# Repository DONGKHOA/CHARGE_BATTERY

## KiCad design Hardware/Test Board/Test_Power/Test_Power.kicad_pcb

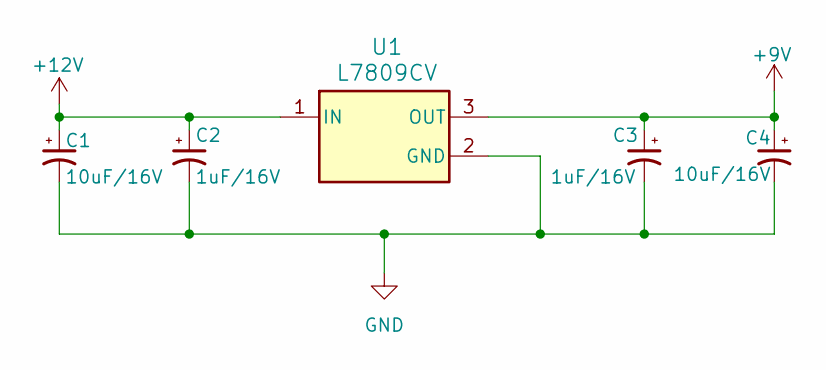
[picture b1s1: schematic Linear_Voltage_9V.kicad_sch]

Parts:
C1, C4: 10uF/16V; Tan_Cap_A
C2, C3: 1uF/16V; Tan_Cap_A
U1: L7809CV; TO-220-3

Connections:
+9V: C3.1, C4.1, U1.3 (OUT); also elsewhere on the board
+12V: C1.1, C2.1, U1.1 (IN); also elsewhere on the board

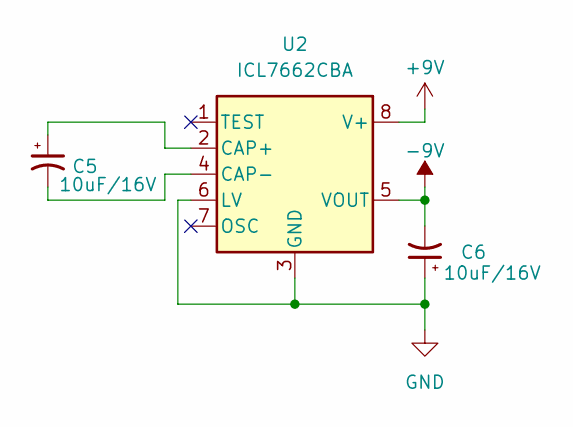
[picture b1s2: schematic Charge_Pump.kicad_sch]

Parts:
C5, C6: 10uF/16V; Tan_Cap_A
U2: ICL7662CBA; SOIC-8

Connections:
+9V: U2.8 (V+); also elsewhere on the board
-9V: C6.2, U2.5 (VOUT); also elsewhere on the board
unnamed: C5.1, U2.2 (CAP+)
unnamed: C5.2, U2.4 (CAP-)

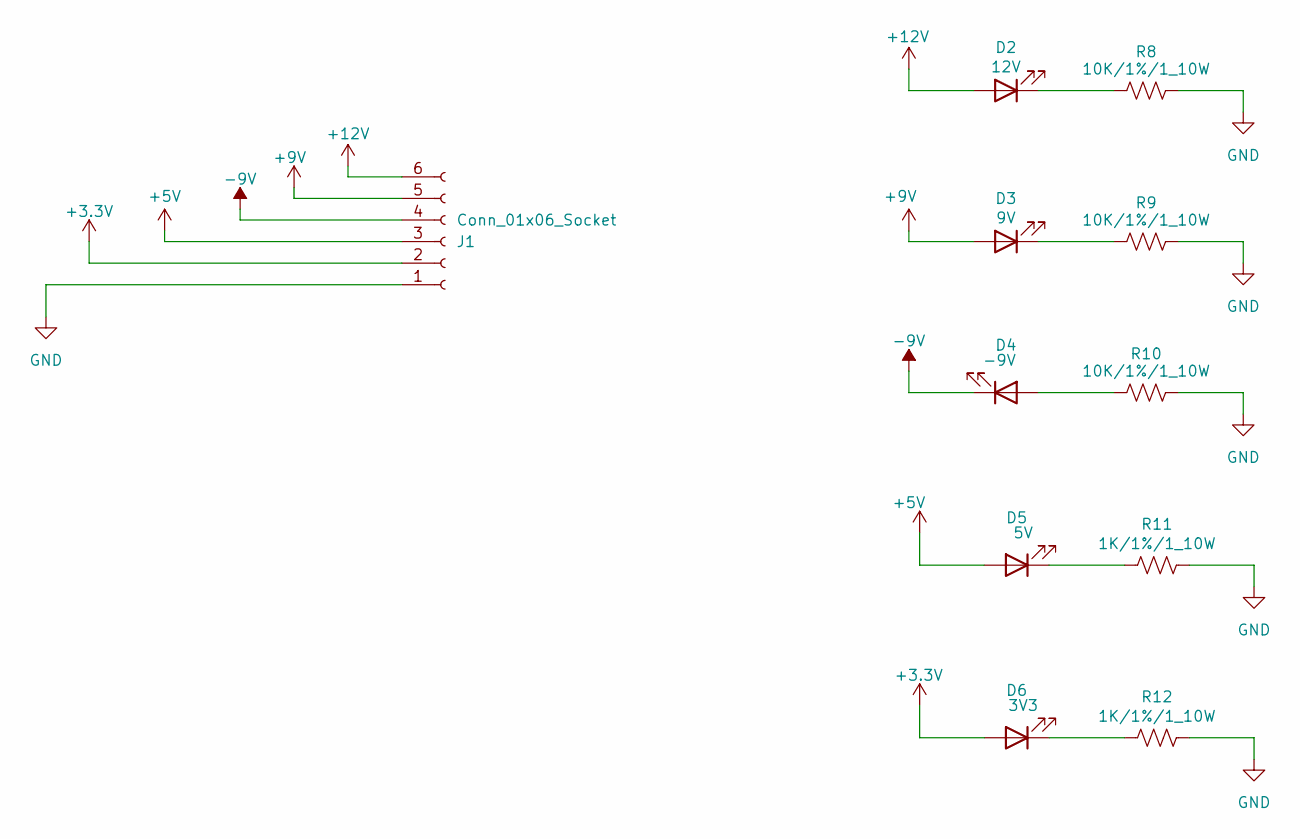
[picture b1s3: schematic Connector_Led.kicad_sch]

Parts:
D2: 12V; LED_0805
D3: 9V; LED_0805
D4: -9V; LED_0805
D5: 5V; LED_0805
D6: 3V3; LED_0805
J1: Conn_01x06_Socket; PhoenixContact_MC_1,5_6-G-3.81_1x06_P3.81mm_Horizontal
R8, R9, R10: 10K/1%/1_10W; Res_0603
R11, R12: 1K/1%/1_10W; Res_0603

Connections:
+3.3V: D6.2 (A), J1.2; also elsewhere on the board
+5V: D5.2 (A), J1.3; also elsewhere on the board
+9V: D3.2 (A), J1.5; also elsewhere on the board
+12V: D2.2 (A), J1.6; also elsewhere on the board
-9V: D4.1 (K), J1.4; also elsewhere on the board
unnamed: D2.1 (K), R8.1
unnamed: D3.1 (K), R9.1
unnamed: D4.2 (A), R10.1
unnamed: D5.1 (K), R11.1
unnamed: D6.1 (K), R12.1

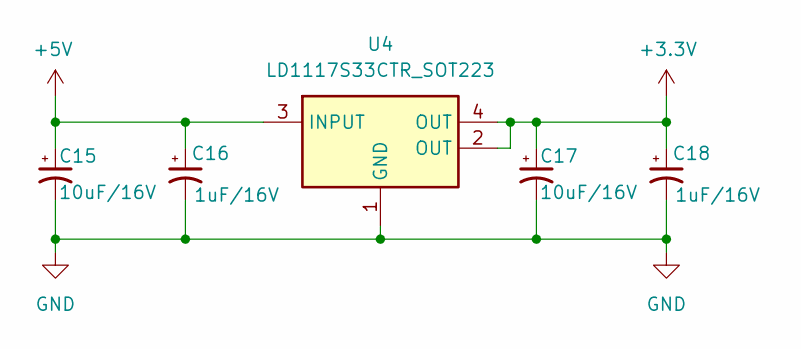
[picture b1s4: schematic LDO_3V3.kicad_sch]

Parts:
C15, C17: 10uF/16V; Tan_Cap_A
C16, C18: 1uF/16V; Tan_Cap_A
U4: LD1117S33CTR_SOT223; SOT-223

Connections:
+3.3V: C17.1, C18.1, U4.2 (OUT), U4.4 (OUT); also elsewhere on the board
+5V: C15.1, C16.1, U4.3 (INPUT); also elsewhere on the board

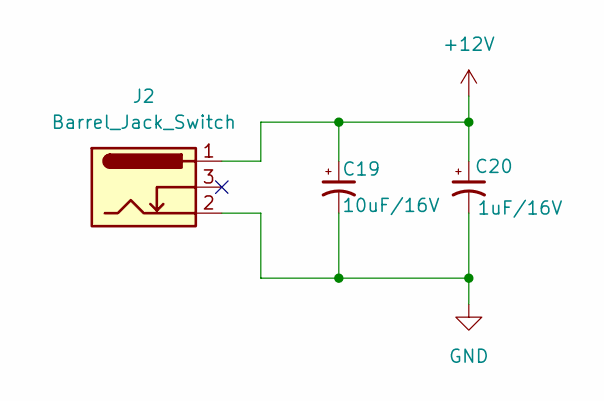
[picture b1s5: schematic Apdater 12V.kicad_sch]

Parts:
C19: 10uF/16V; Tan_Cap_A
C20: 1uF/16V; Tan_Cap_A
J2: Barrel_Jack_Switch; BarrelJack_GCT_DCJ200-10-A_Horizontal

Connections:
+12V: C19.1, C20.1, J2.1; also elsewhere on the board

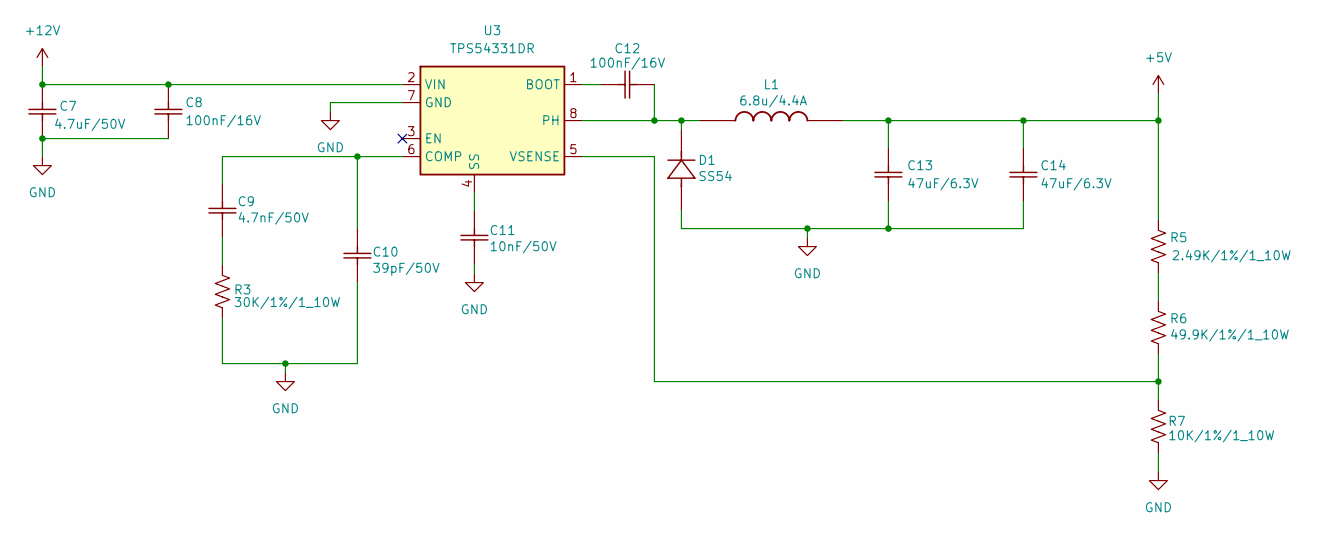
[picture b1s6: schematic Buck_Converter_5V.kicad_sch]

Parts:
C7: 4.7uF/50V; Ceramic_Cap_0805
C8, C12: 100nF/16V; Ceramic_Cap_0603
C9: 4.7nF/50V; Ceramic_Cap_0603
C10: 39pF/50V; Ceramic_Cap_0603
C11: 10nF/50V; Ceramic_Cap_0603
C13, C14: 47uF/6.3V; Ceramic_Cap_0805
D1: SS54; D_SMA
L1: 6.8u/4.4A; Inductor_6.8u_4.4A
R3: 30K/1%/1_10W; Res_0603
R5: 2.49K/1%/1_10W; Res_0603
R6: 49.9K/1%/1_10W; Res_0603
R7: 10K/1%/1_10W; Res_0603
U3: TPS54331DR; SOIC-8

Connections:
+5V: C13.2, C14.2, L1.2, R5.2; also elsewhere on the board
+12V: C7.2, C8.2, U3.2 (VIN); also elsewhere on the board
unnamed: C9.1, R3.2
unnamed: C12.2, D1.2 (K), L1.1, U3.8 (PH)
unnamed: R5.1, R6.2
unnamed: C12.1, U3.1 (BOOT)
unnamed: C9.2, C10.2, U3.6 (COMP)
unnamed: C11.2, U3.4 (SS)

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
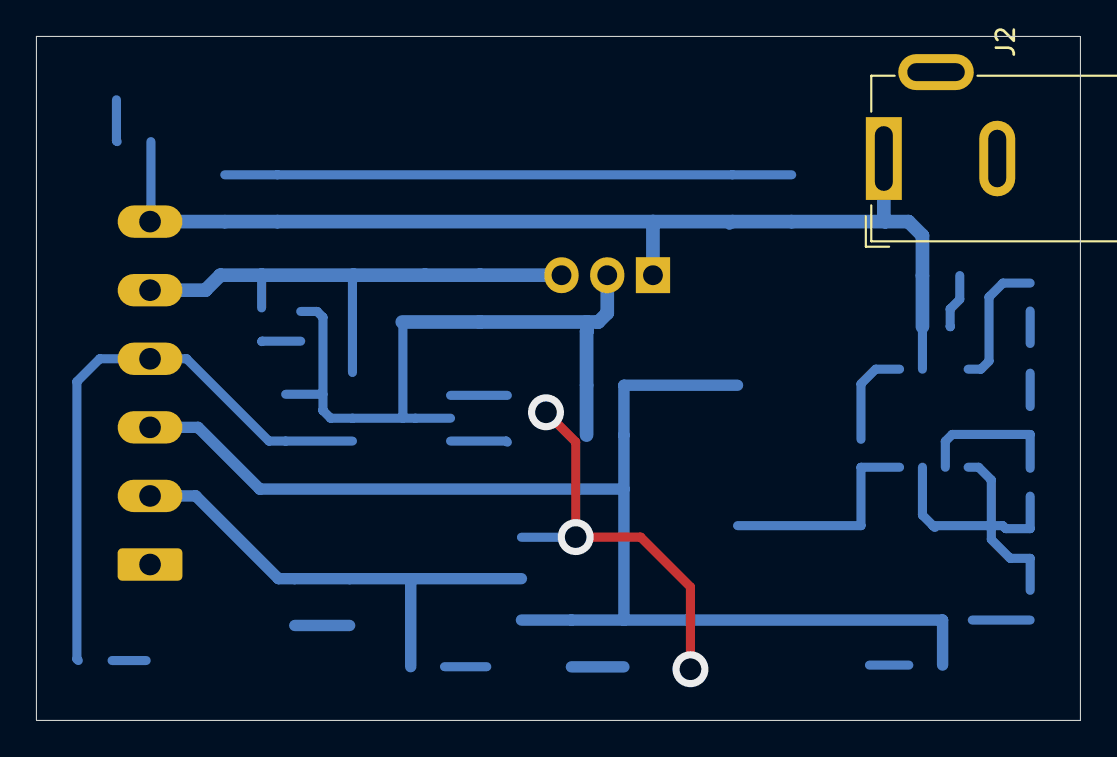
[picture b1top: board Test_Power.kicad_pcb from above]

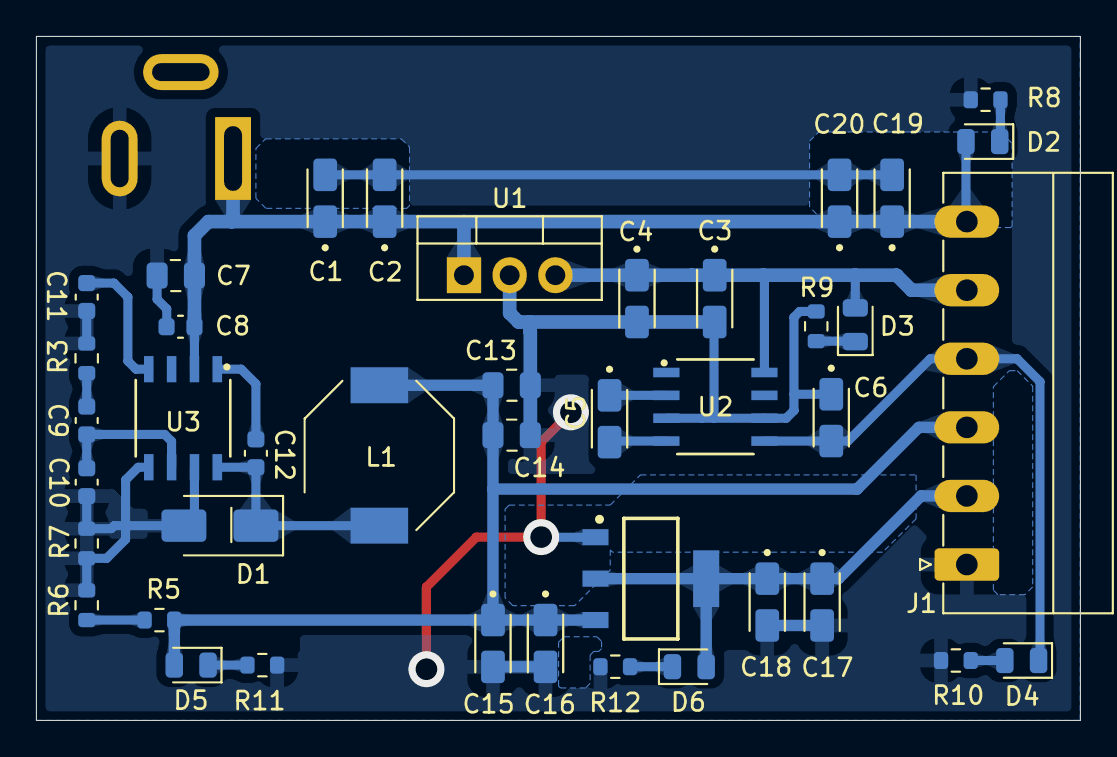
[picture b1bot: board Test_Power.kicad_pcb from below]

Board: 2 copper layers, 58.0 x 38.0 mm, 42 parts (41 on the bottom side), 19 nets.

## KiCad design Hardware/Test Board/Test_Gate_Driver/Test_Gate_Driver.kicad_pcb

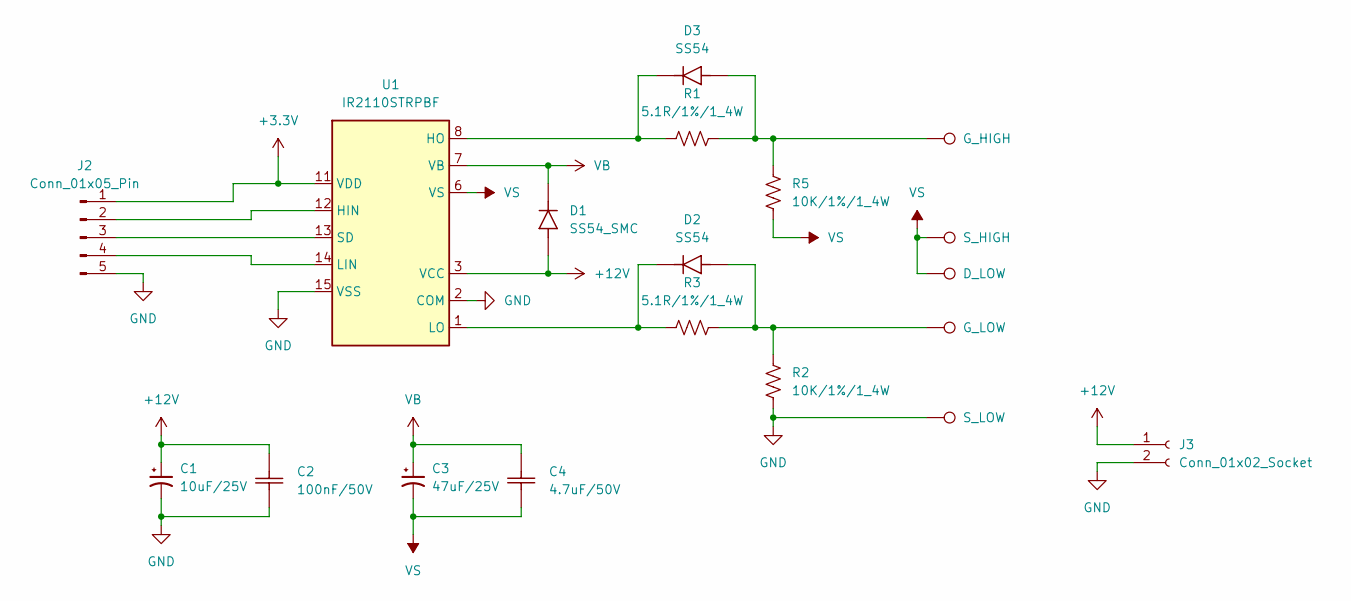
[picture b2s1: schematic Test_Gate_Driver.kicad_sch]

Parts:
C1: 10uF/25V; CP_Elec_4x5.4
C2: 100nF/50V; Ceramic_Cap_1206
C3: 47uF/25V; CP_Elec_6.3x5.4
C4: 4.7uF/50V; Ceramic_Cap_1206
D1: SS54_SMC; D_SMC
D2, D3: SS54; D_SMA
J2: Conn_01x05_Pin; PinHeader_1x05_P2.54mm_Vertical
J3: Conn_01x02_Socket; PinHeader_1x02_P2.54mm_Vertical
R1, R3: 5.1R/1%/1_4W; Res_1206
R2, R5: 10K/1%/1_4W; Res_1206
TP1: G_HIGH; TestPoint_Pad_3.0x3.0mm
TP2: S_HIGH; TestPoint_Pad_3.0x3.0mm
TP3: G_LOW; TestPoint_Pad_3.0x3.0mm
TP4: S_LOW; TestPoint_Pad_3.0x3.0mm
TP5: D_LOW; TestPoint_Pad_3.0x3.0mm
U1: IR2110STRPBF; SOP-16

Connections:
+3.3V: J2.1, U1.11 (VDD)
+12V: C1.1, C2.2, D1.1 (A), J3.1, U1.3 (VCC)
GND: C1.2, C2.1, J2.5, J3.2, R2.1, TP4.1, U1.2 (COM), U1.15 (VSS)
unnamed: D2.1 (A), R2.2, R3.2, TP3.1
unnamed: D2.2 (K), R3.1, U1.1 (LO)
unnamed: D3.1 (A), R1.2, R5.2, TP1.1
unnamed: D3.2 (K), R1.1, U1.8 (HO)
unnamed: J2.2, U1.12 (HIN)
unnamed: J2.3, U1.13 (SD)
unnamed: J2.4, U1.14 (LIN)
VB: C3.1, C4.1, D1.2 (K), U1.7 (VB)
VS: C3.2, C4.2, R5.1, TP2.1, TP5.1, U1.6 (VS)

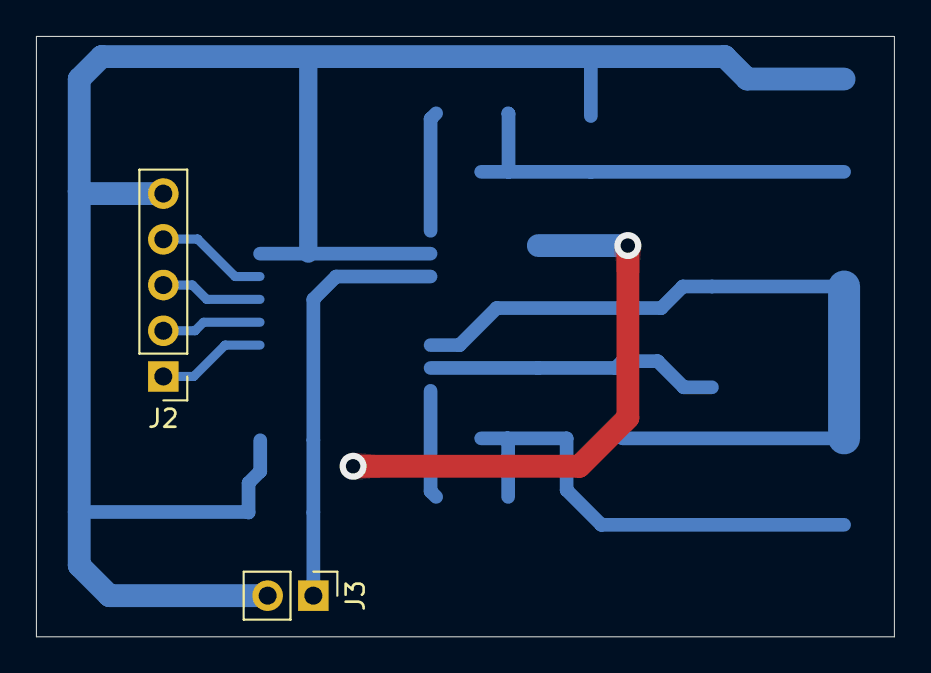
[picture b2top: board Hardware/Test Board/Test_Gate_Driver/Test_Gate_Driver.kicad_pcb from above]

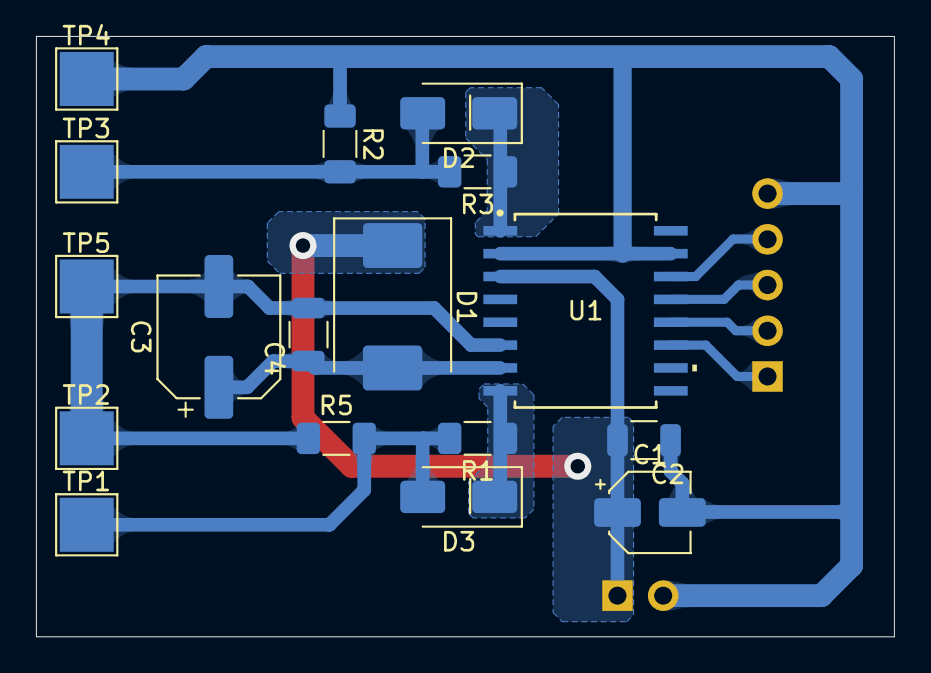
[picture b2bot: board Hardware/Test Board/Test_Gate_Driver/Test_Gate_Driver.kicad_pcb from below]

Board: 2 copper layers, 47.7 x 33.4 mm, 19 parts (17 on the bottom side), 12 nets.

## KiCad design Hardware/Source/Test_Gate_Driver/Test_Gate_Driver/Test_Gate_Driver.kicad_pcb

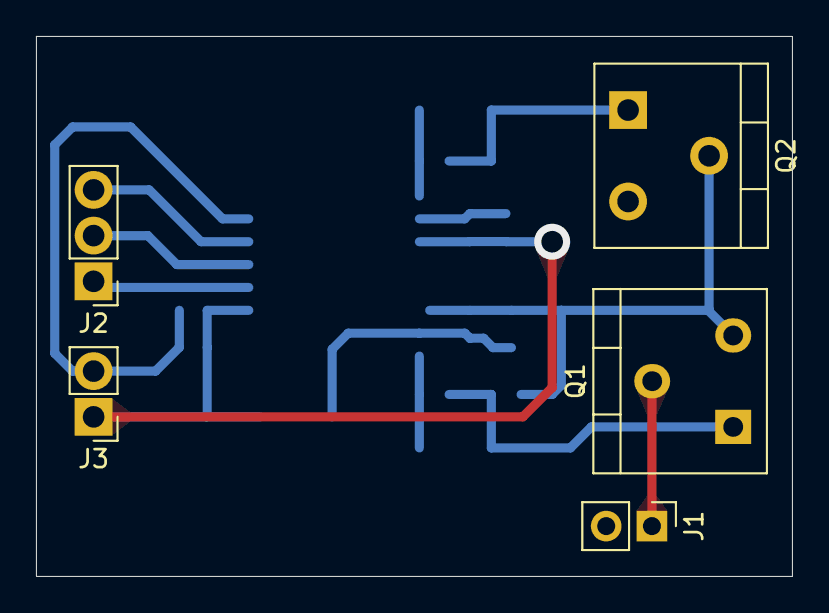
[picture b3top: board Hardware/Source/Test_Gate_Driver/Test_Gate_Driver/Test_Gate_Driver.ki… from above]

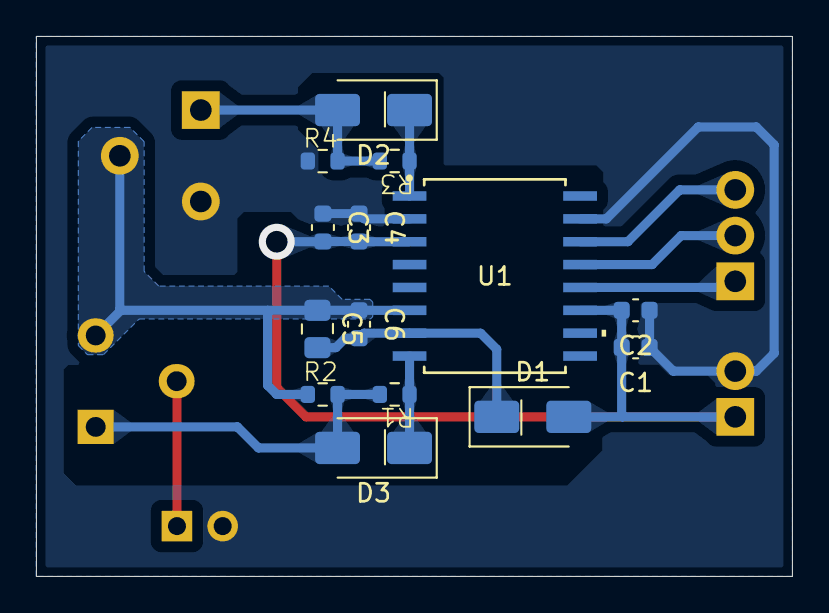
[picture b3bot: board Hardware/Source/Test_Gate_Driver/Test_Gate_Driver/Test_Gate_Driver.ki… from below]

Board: 2 copper layers, 42.0 x 30.0 mm, 19 parts (14 on the bottom side), 12 nets.

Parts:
C1, C3: 10uF/16V; Ceramic_Cap_0603
C2, C4: 100nF/16V; Ceramic_Cap_0603
C5: 22uF/16V; Ceramic_Cap_0805
C6: 4.7uF/25V; Ceramic_Cap_0603
D1, D2, D3: SS54; D_SMA
J1, J3: Conn_01x02_Socket; PinHeader_1x02_P2.54mm_Vertical
J2: Conn_01x03_Socket; PinHeader_1x03_P2.54mm_Vertical
Q1, Q2: IPP60R125CP; TO-220-3
R1, R3: 10R/1%/1_10W; Res_0603
R2, R4: 10K/1%/1_10W; Res_0603
U1: IR2110STRPBF; SOP-16

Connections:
+12V: C1.2, C2.2, C3.2, C4.2, D1.1 (A), J3.1, U1.3 (VCC), U1.11 (VDD)
+VDC: J1.1, Q1.2 (D)
GND: C1.1, C2.1, C3.1, C4.1, J1.2, J3.2, Q2.3 (S), R4.1, U1.2 (COM), U1.15 (VSS)
unnamed: D2.1 (A), Q2.1 (G), R3.2, R4.2
unnamed: D2.2 (K), R3.1, U1.1 (LO)
unnamed: D3.1 (A), Q1.1 (G), R1.2, R2.2
unnamed: D3.2 (K), R1.1, U1.8 (HO)
unnamed: J2.1, U1.12 (HIN)
unnamed: J2.2, U1.13 (SD)
unnamed: J2.3, U1.14 (LIN)
VD: C5.2, C6.2, D1.2 (K), U1.7 (VB)
VS: C5.1, C6.1, Q1.3 (S), Q2.2 (D), R2.1, U1.6 (VS)

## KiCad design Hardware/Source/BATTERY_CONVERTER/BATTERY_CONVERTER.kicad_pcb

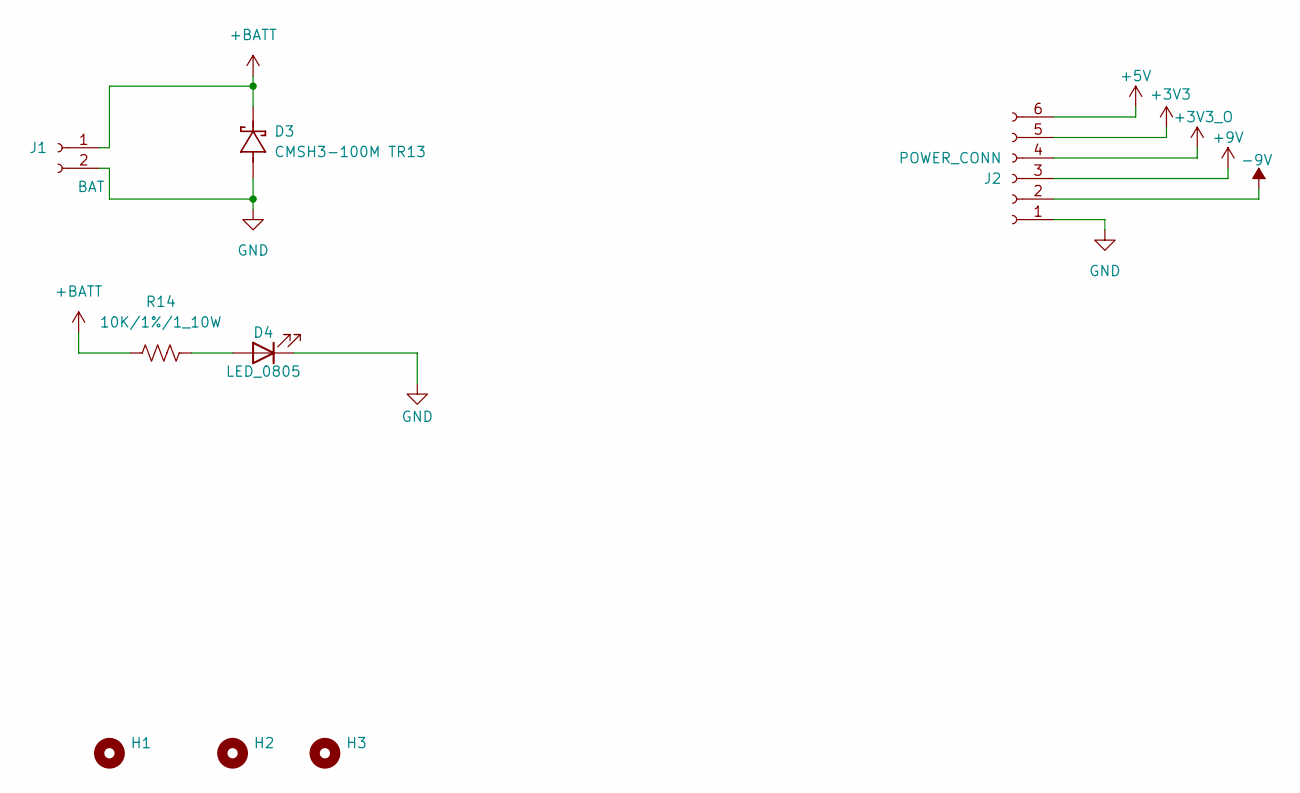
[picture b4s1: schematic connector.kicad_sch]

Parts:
D3: CMSH3-100M TR13; D_SMB
D4: LED_0805
H1, H2, H3: MountingHole; MountingHole_3.2mm_M3_Pad_Via
J1: BAT; PhoenixContact_MC_1,5_2-G-3.81_1x02_P3.81mm_Horizontal
J2: POWER_CONN; PhoenixContact_MC_1,5_6-G-3.81_1x06_P3.81mm_Horizontal
R14: 10K/1%/1_10W; Res_0603

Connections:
+3V3: J2.5; also elsewhere on the board
+3V3_O: J2.4; also elsewhere on the board
+5V: J2.6; also elsewhere on the board
+9V: J2.3; also elsewhere on the board
+BATT: D3.2 (K), J1.1, R14.1; also elsewhere on the board
-9V: J2.2; also elsewhere on the board
GND: D3.1 (A), D4.1 (K), J1.2, J2.1; also elsewhere on the board
unnamed: D4.2 (A), R14.2

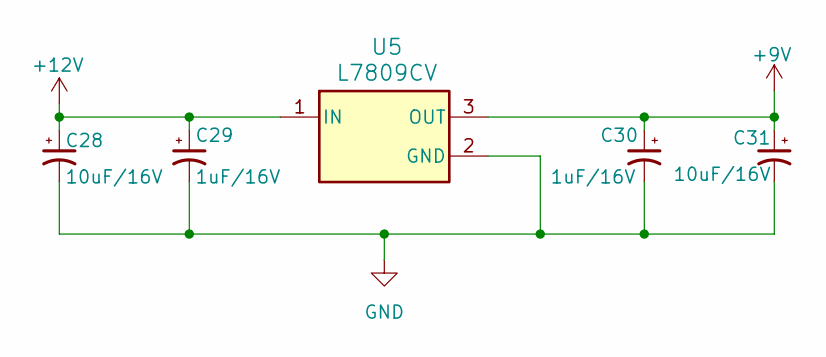
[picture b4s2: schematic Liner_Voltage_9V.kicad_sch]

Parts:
C28, C31: 10uF/16V; Tan_Cap_A
C29, C30: 1uF/16V; Tan_Cap_A
U5: L7809CV; TO-220-3_Horizontal_TabDown

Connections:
+9V: C30.1, C31.1, U5.3 (OUT); also elsewhere on the board
+12V: C28.1, C29.1, U5.1 (IN); also elsewhere on the board
GND: C28.2, C29.2, C30.2, C31.2, U5.2 (GND); also elsewhere on the board

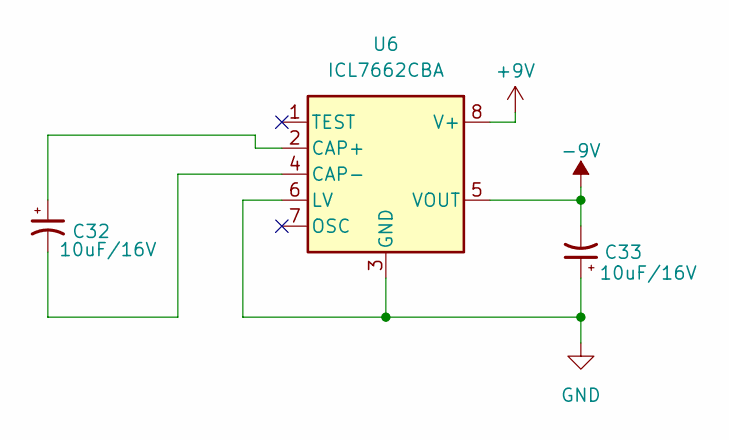
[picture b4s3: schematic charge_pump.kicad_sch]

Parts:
C32, C33: 10uF/16V; Tan_Cap_A
U6: ICL7662CBA; SOIC-8

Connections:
+9V: U6.8 (V+); also elsewhere on the board
-9V: C33.2, U6.5 (VOUT); also elsewhere on the board
GND: C33.1, U6.3 (GND), U6.6 (LV); also elsewhere on the board
unnamed: C32.1, U6.2 (CAP+)
unnamed: C32.2, U6.4 (CAP-)

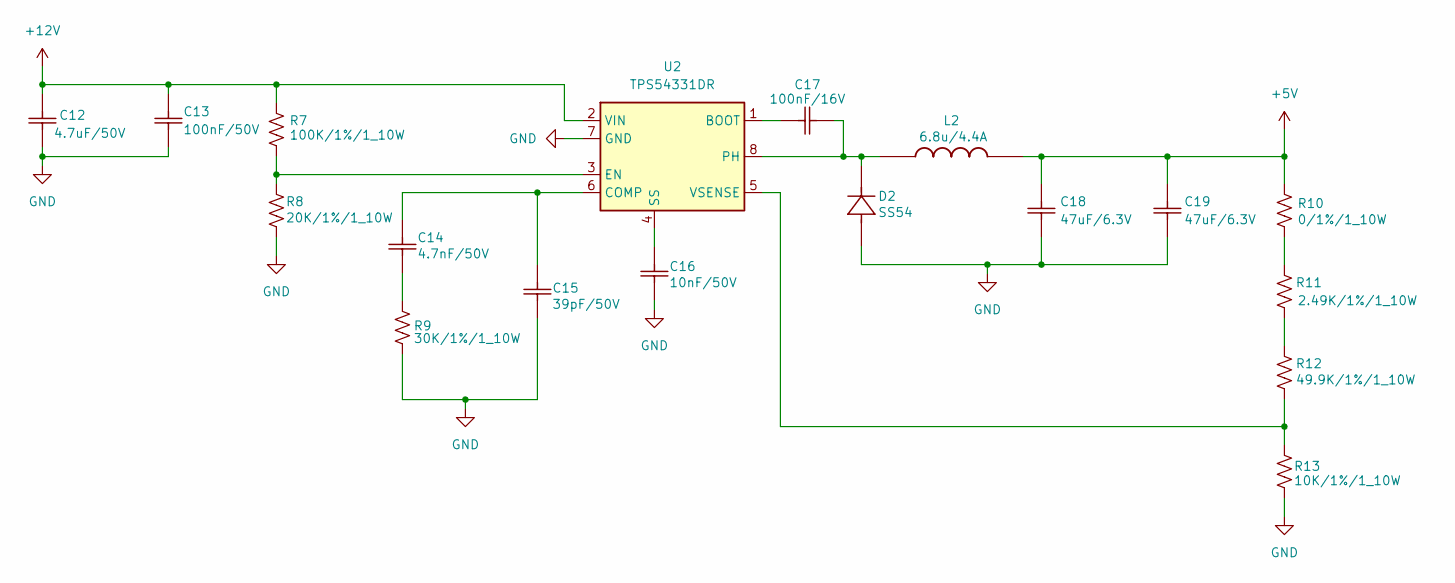
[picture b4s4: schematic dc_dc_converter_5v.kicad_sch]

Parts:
C12: 4.7uF/50V; Ceramic_Cap_0805
C13: 100nF/50V; Ceramic_Cap_0805
C14: 4.7nF/50V; Ceramic_Cap_0603
C15: 39pF/50V; Ceramic_Cap_0603
C16: 10nF/50V; Ceramic_Cap_0603
C17: 100nF/16V; Ceramic_Cap_0603
C18, C19: 47uF/6.3V; Ceramic_Cap_0805
D2: SS54; D_SMA
L2: 6.8u/4.4A; Inductor_6.8u_4.4A
R7: 100K/1%/1_10W; Res_0603
R8: 20K/1%/1_10W; Res_0603
R9: 30K/1%/1_10W; Res_0603
R10: 0/1%/1_10W; Res_0603
R11: 2.49K/1%/1_10W; Res_0603
R12: 49.9K/1%/1_10W; Res_0603
R13: 10K/1%/1_10W; Res_0603
U2: TPS54331DR; SOIC-8

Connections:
+5V: C18.2, C19.2, L2.2, R10.2; also elsewhere on the board
+12V: C12.2, C13.2, R7.2, U2.2 (VIN); also elsewhere on the board
GND: C12.1, C13.1, C15.1, C16.1, C18.1, C19.1, D2.1 (A), R8.1, R9.1, R13.1, U2.7 (GND); also elsewhere on the board
unnamed: C14.1, R9.2
unnamed: C17.2, D2.2 (K), L2.1, U2.8 (PH)
unnamed: R10.1, R11.2
unnamed: R11.1, R12.2
unnamed: C17.1, U2.1 (BOOT)
unnamed: C14.2, C15.2, U2.6 (COMP)
unnamed: R7.1, R8.2, U2.3 (EN)
unnamed: C16.2, U2.4 (SS)
unnamed: R12.1, R13.2, U2.5 (VSENSE)

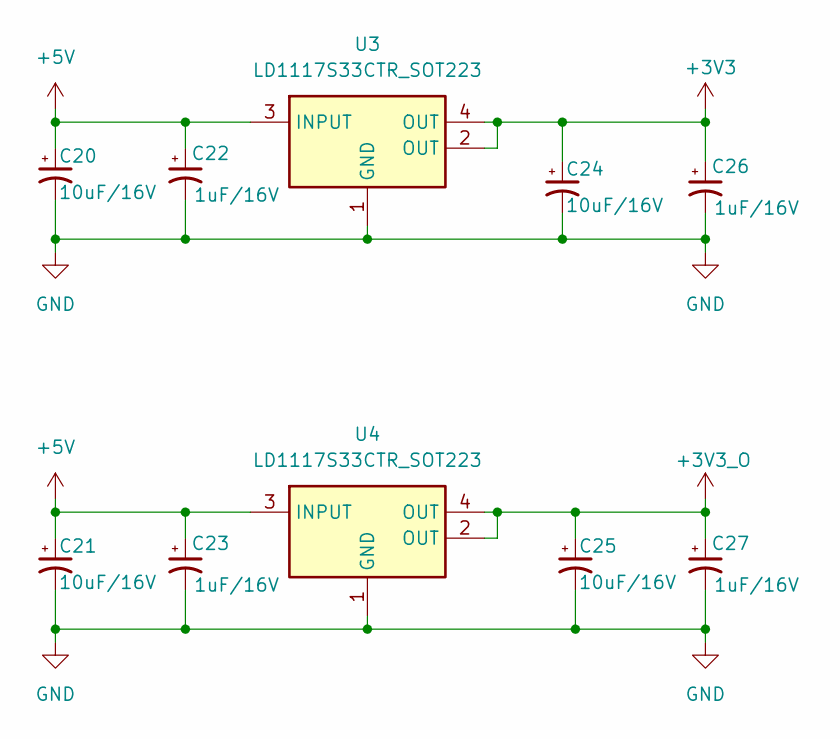
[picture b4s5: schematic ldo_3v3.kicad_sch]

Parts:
C20, C21, C24, C25: 10uF/16V; Tan_Cap_A
C22, C23, C26, C27: 1uF/16V; Tan_Cap_A
U3, U4: LD1117S33CTR_SOT223; SOT-223

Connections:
+3V3: C24.1, C26.1, U3.2 (OUT), U3.4 (OUT); also elsewhere on the board
+3V3_O: C25.1, C27.1, U4.2 (OUT), U4.4 (OUT); also elsewhere on the board
+5V: C20.1, C21.1, C22.1, C23.1, U3.3 (INPUT), U4.3 (INPUT); also elsewhere on the board
GND: C20.2, C21.2, C22.2, C23.2, C24.2, C25.2, C26.2, C27.2, U3.1 (GND), U4.1 (GND); also elsewhere on the board

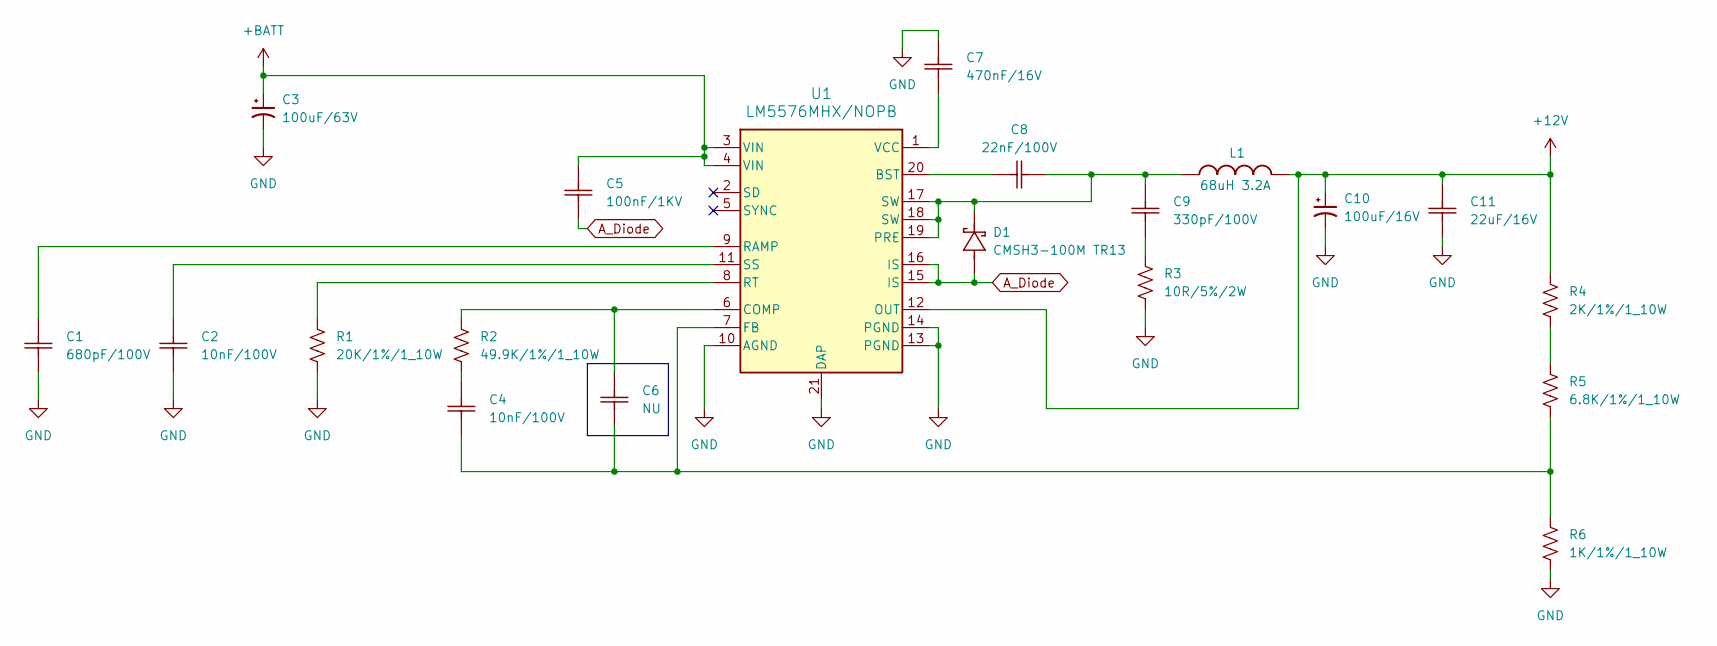
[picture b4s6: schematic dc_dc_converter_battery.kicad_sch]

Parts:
C1: 680pF/100V; Ceramic_Cap_0603
C2, C4: 10nF/100V; Ceramic_Cap_0603
C3: 100uF/63V; CP_Elec_10x10.5
C5: 100nF/1KV; Ceramic_Cap_1812
C6: NU; Ceramic_Cap_0603
C7: 470nF/16V; Ceramic_Cap_0603
C8: 22nF/100V; Ceramic_Cap_0805
C9: 330pF/100V; Ceramic_Cap_0603
C10: 100uF/16V; CP_Elec_6.3x5.4
C11: 22uF/16V; Ceramic_Cap_0805
D1: CMSH3-100M TR13; D_SMB
L1: 68uH 3.2A; IND_CDRH127_LDNP-470MC_SUM
R1: 20K/1%/1_10W; Res_0603
R2: 49.9K/1%/1_10W; Res_0603
R3: 10R/5%/2W; Res_Hole_2W
R4: 2K/1%/1_10W; Res_0603
R5: 6.8K/1%/1_10W; Res_0603
R6: 1K/1%/1_10W; Res_0603
U1: LM5576MHX/NOPB; HTSSOP-20

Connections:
+12V: C10.1, C11.2, L1.2, R4.2, U1.12 (OUT); also elsewhere on the board
+BATT: C3.1, C5.2, U1.3 (VIN), U1.4 (VIN); also elsewhere on the board
A_Diode: C5.1, D1.1 (A), U1.15 (IS), U1.16 (IS)
GND: C1.1, C2.1, C3.2, C7.2, C10.2, C11.1, R1.1, R3.1, R6.1, U1.10 (AGND), U1.13 (PGND), U1.14 (PGND), U1.21 (DAP); also elsewhere on the board
unnamed: C4.2, R2.1
unnamed: C9.1, R3.2
unnamed: C8.2, C9.2, D1.2 (K), L1.1, U1.17 (SW), U1.18 (SW), U1.19 (PRE)
unnamed: R4.1, R5.2
unnamed: C8.1, U1.20 (BST)
unnamed: C6.2, R2.2, U1.6 (COMP)
unnamed: C4.1, C6.1, R5.1, R6.2, U1.7 (FB)
unnamed: C1.2, U1.9 (RAMP)
unnamed: R1.2, U1.8 (RT)
unnamed: C2.2, U1.11 (SS)
unnamed: C7.1, U1.1 (VCC)

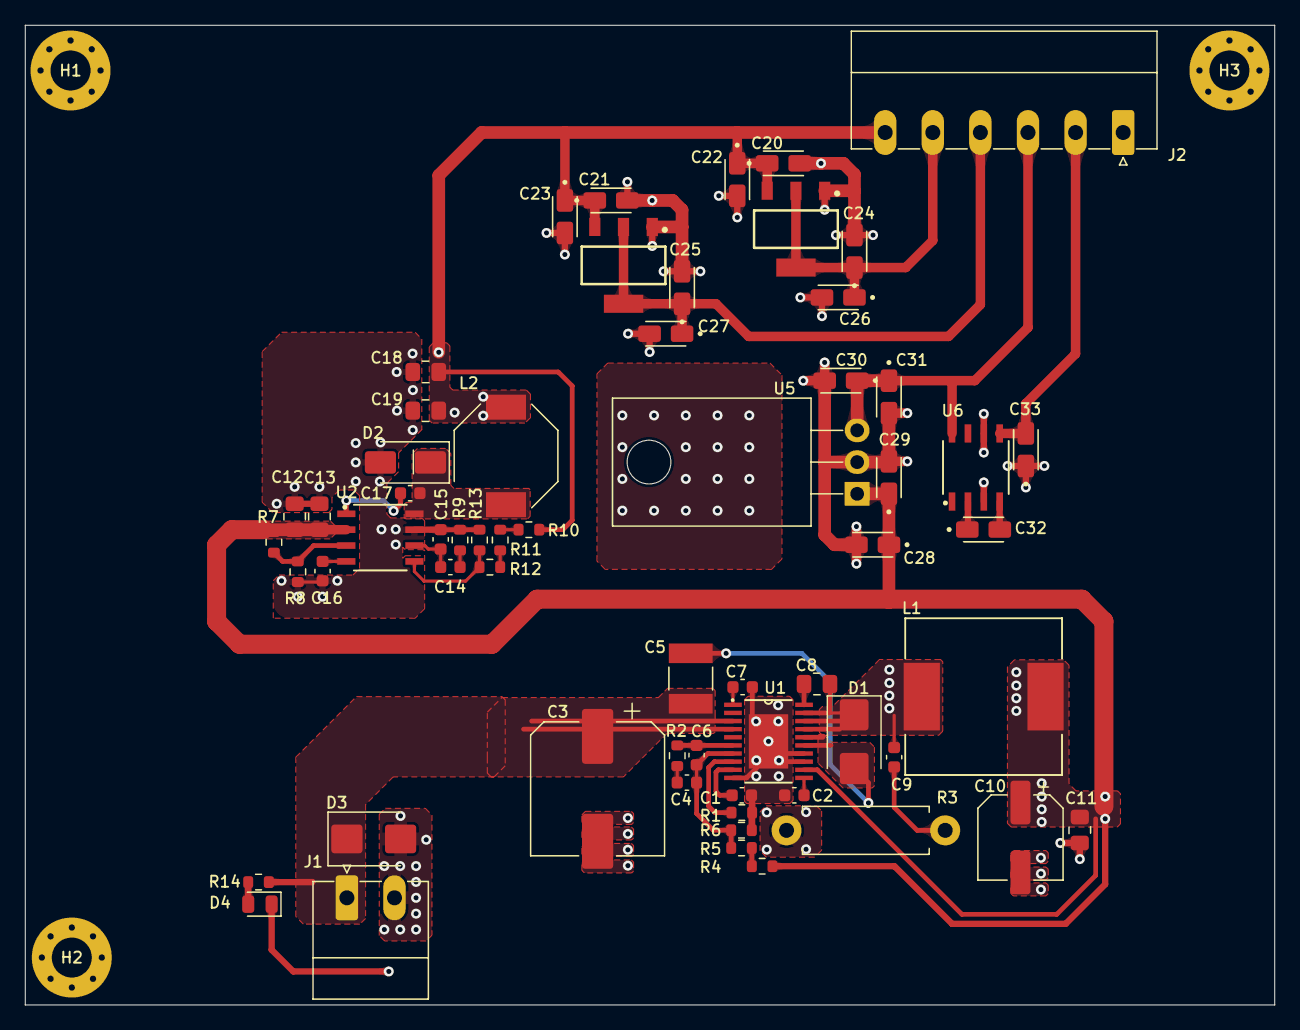
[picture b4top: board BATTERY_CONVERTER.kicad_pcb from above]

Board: 2 copper layers, 100.0 x 78.4 mm, 64 parts (0 on the bottom side), 32 nets.
